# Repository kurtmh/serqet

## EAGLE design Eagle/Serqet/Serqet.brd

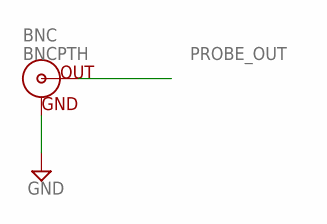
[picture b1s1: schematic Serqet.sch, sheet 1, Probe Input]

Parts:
BNC: BNCPTH; BNC

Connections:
GND: BNC.GND; also elsewhere on the board
PROBE_OUT: BNC.S (OUT); also elsewhere on the board

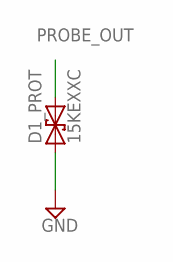
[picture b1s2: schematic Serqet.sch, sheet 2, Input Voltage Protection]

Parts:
D1_PROT: 15KEXXC; CB429-17

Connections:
GND: D1_PROT.A (1); also elsewhere on the board
PROBE_OUT: D1_PROT.C (2); also elsewhere on the board

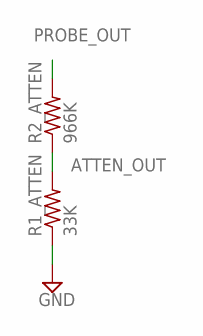
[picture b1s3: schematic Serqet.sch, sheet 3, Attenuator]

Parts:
R1_ATTEN: 33K; R0603
R2_ATTEN: 966K; R0603

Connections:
ATTEN_OUT: R1_ATTEN.2, R2_ATTEN.1; also elsewhere on the board
GND: R1_ATTEN.1; also elsewhere on the board
PROBE_OUT: R2_ATTEN.2; also elsewhere on the board

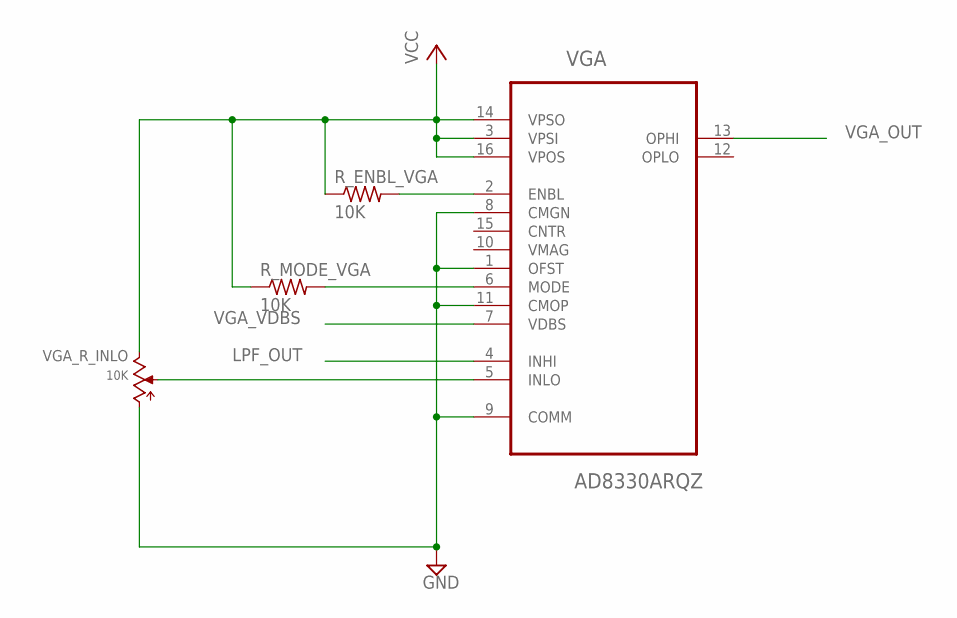
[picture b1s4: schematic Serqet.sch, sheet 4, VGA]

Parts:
R_ENBL_VGA: 10K; R0603
R_MODE_VGA: 10K; R0603
VGA: AD8330ARQZ; SOP63P600X175-16N
VGA_R_INLO: 10K; TRIMPOT:3HOLE_CHEAP

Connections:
GND: VGA.1 (OFST), VGA.8 (CMGN), VGA.9 (COMM), VGA.11 (CMOP), VGA_R_INLO.CCW; also elsewhere on the board
LPF_OUT: VGA.4 (INHI); also elsewhere on the board
unnamed: VGA.5 (INLO), VGA_R_INLO.W
unnamed: R_ENBL_VGA.2, VGA.2 (ENBL)
VCC: R_ENBL_VGA.1, R_MODE_VGA.1, VGA.3 (VPSI), VGA.14 (VPSO), VGA.16 (VPOS), VGA_R_INLO.CW; also elsewhere on the board
VGA_MODE: R_MODE_VGA.2, VGA.6 (MODE)
VGA_OUT: VGA.13 (OPHI); also elsewhere on the board
VGA_VDBS: VGA.7 (VDBS); also elsewhere on the board

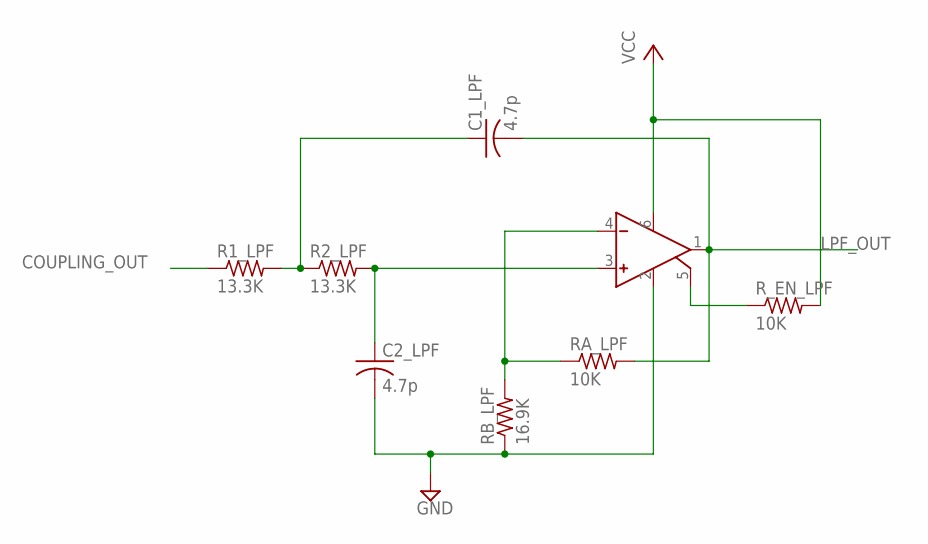
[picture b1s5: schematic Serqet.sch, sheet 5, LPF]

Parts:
C1_LPF, C2_LPF: 4.7p; C0603
OP_AMP_LPF: OPA355; SOT23-6
R1_LPF, R2_LPF: 13.3K; R0603
RA_LPF: 10K; R0603
RB_LPF: 16.9K; R0603
R_EN_LPF: 10K; R0603

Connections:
COUPLING_OUT: R1_LPF.1; also elsewhere on the board
GND: C2_LPF.2, OP_AMP_LPF.2 (GND), RB_LPF.1; also elsewhere on the board
LPF_OUT: C1_LPF.2, OP_AMP_LPF.1 (OUT), RA_LPF.2; also elsewhere on the board
unnamed: C2_LPF.1, OP_AMP_LPF.3 (V+), R2_LPF.2
unnamed: C1_LPF.1, R1_LPF.2, R2_LPF.1
unnamed: OP_AMP_LPF.4 (V-), RA_LPF.1, RB_LPF.2
unnamed: OP_AMP_LPF.5 (ENABLE), R_EN_LPF.1
VCC: OP_AMP_LPF.6 (VCC), R_EN_LPF.2; also elsewhere on the board

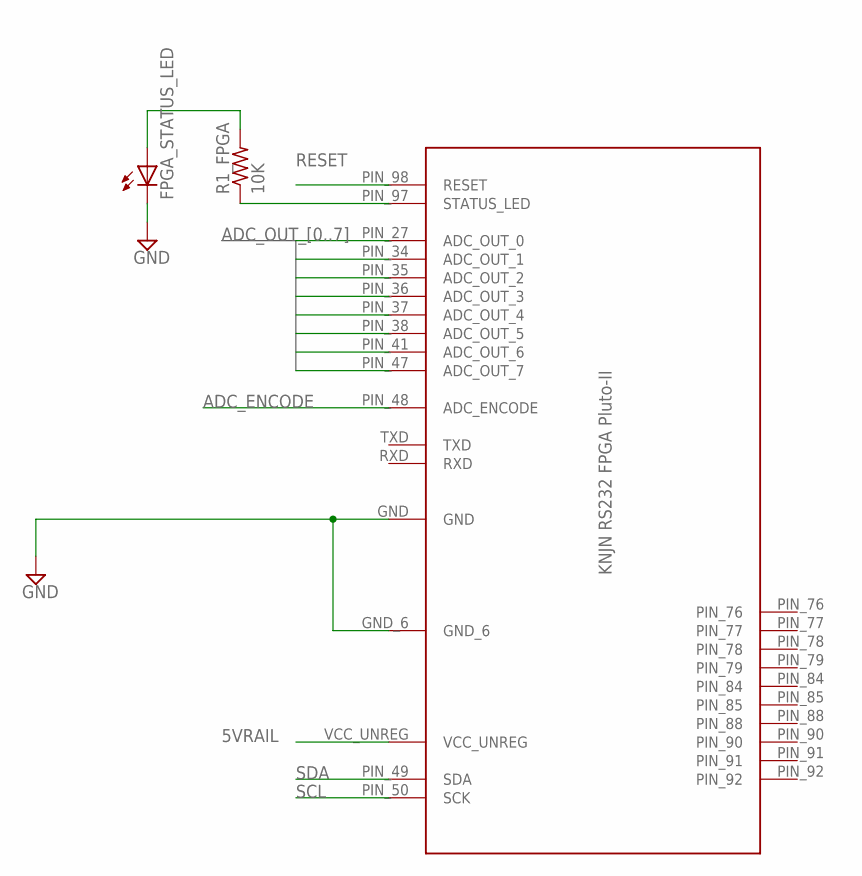
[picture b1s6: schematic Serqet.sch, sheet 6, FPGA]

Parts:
FPGA: KNJNRS232FPGAPLUTO-IIKNJNRS232FPGAPLUTO-II; KNJNRS232FPGAPLUTO-II
FPGA_STATUS_LED: LEDCHIP-LED0805; CHIP-LED0805
R1_FPGA: 10K; R0603

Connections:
5VRAIL: FPGA.VCC_UNREG; also elsewhere on the board
ADC_ENCODE: FPGA.PIN_48 (ADC_ENCODE); also elsewhere on the board
ADC_OUT_0: FPGA.PIN_47 (ADC_OUT_7); also elsewhere on the board
ADC_OUT_1: FPGA.PIN_41 (ADC_OUT_6); also elsewhere on the board
ADC_OUT_2: FPGA.PIN_38 (ADC_OUT_5); also elsewhere on the board
ADC_OUT_3: FPGA.PIN_37 (ADC_OUT_4); also elsewhere on the board
ADC_OUT_4: FPGA.PIN_36 (ADC_OUT_3); also elsewhere on the board
ADC_OUT_5: FPGA.PIN_35 (ADC_OUT_2); also elsewhere on the board
ADC_OUT_6: FPGA.PIN_34 (ADC_OUT_1); also elsewhere on the board
ADC_OUT_7: FPGA.PIN_27 (ADC_OUT_0); also elsewhere on the board
GND: FPGA.GND, FPGA.GND_6, FPGA_STATUS_LED.C; also elsewhere on the board
unnamed: FPGA.PIN_97 (STATUS_LED), R1_FPGA.1
unnamed: FPGA_STATUS_LED.A, R1_FPGA.2
RESET: FPGA.PIN_98 (RESET); also elsewhere on the board
SCL: FPGA.PIN_50 (SCK); also elsewhere on the board
SDA: FPGA.PIN_49 (SDA); also elsewhere on the board

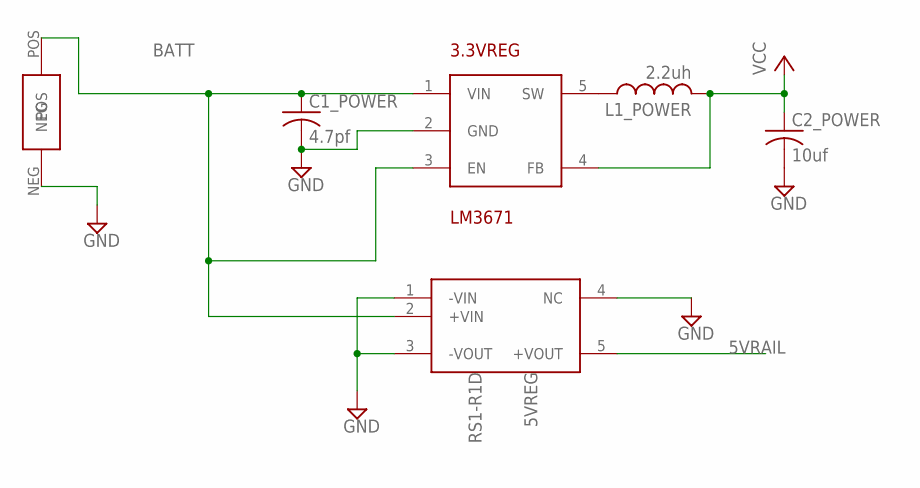
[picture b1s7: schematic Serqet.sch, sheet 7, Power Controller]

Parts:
3.3VREG: LM3671; SOT23-5
5VREG: RS1-R1D; 8-SMD
BATTERY: LED_THROUGHHOLE
C1_POWER: 4.7pf; C0603
C2_POWER: 10uf; C0603
L1_POWER: 2.2uh; L1812

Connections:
5VRAIL: 5VREG.5 (+VOUT); also elsewhere on the board
BATT: 3.3VREG.1 (VIN), 3.3VREG.3 (EN), 5VREG.2 (+VIN), BATTERY.POS, C1_POWER.1
GND: 3.3VREG.2 (GND), 5VREG.1 (-VIN), 5VREG.3 (-VOUT), 5VREG.4 (NC), BATTERY.NEG, C1_POWER.2, C2_POWER.2; also elsewhere on the board
unnamed: 3.3VREG.5 (SW), L1_POWER.1
VCC: 3.3VREG.4 (FB), C2_POWER.1, L1_POWER.2; also elsewhere on the board

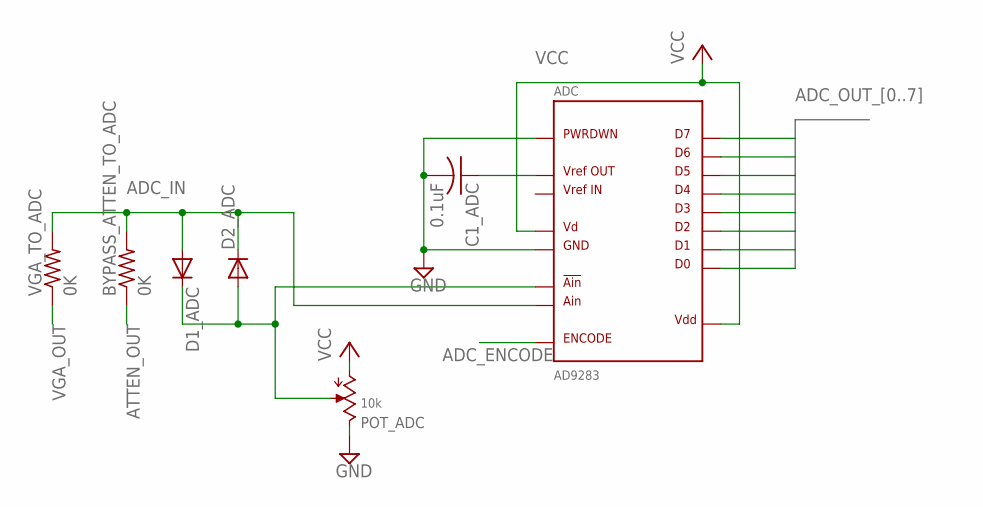
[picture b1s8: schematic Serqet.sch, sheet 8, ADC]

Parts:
ADC: AD9283; SSOP20
BYPASS_ATTEN_TO_ADC: 0K; R0603
C1_ADC: 0.1uF; C0603
D1_ADC, D2_ADC: 1N4933; DO41-10
POT_ADC: 10k; TRIMPOT:3HOLE_CHEAP
VGA_TO_ADC: 0K; R0603

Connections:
ADC_ENCODE: ADC.10 (ENCODE); also elsewhere on the board
ADC_IN: ADC.7 (AIN), BYPASS_ATTEN_TO_ADC.2, D1_ADC.A, D2_ADC.C, VGA_TO_ADC.2
ADC_OUT_0: ADC.20 (D0); also elsewhere on the board
ADC_OUT_1: ADC.19 (D1); also elsewhere on the board
ADC_OUT_2: ADC.18 (D2); also elsewhere on the board
ADC_OUT_3: ADC.17 (D3); also elsewhere on the board
ADC_OUT_4: ADC.14 (D4); also elsewhere on the board
ADC_OUT_5: ADC.13 (D5); also elsewhere on the board
ADC_OUT_6: ADC.12 (D6); also elsewhere on the board
ADC_OUT_7: ADC.11 (D7); also elsewhere on the board
ATTEN_OUT: BYPASS_ATTEN_TO_ADC.1; also elsewhere on the board
GND: ADC.1 (PWRDWN), ADC.4 (GND), ADC.9 (GND), ADC.16 (GND), C1_ADC.2, POT_ADC.CW; also elsewhere on the board
unnamed: ADC.2 (VREFOUT), C1_ADC.1
unnamed: ADC.6 (!AIN), D1_ADC.C, D2_ADC.A, POT_ADC.W
VCC: ADC.5 (VD), ADC.8 (VD), ADC.15 (VDD), POT_ADC.CCW; also elsewhere on the board
VGA_OUT: VGA_TO_ADC.1; also elsewhere on the board
VREFIN: ADC.3 (VREFIN)

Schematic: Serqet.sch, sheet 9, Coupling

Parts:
BILATERAL_COUPLING: TC74HC4066AFT; TSSOP14
C1_COUPLING: 9.1nF; C0603
OP_AMP_COUPLING: OPA355; SOT23-6
POT_COUPLING: 10K; TRIMPOT:3HOLE_CHEAP
R1_COUPLING, R2_COUPLING, R3_COUPLING, R4_COUPLING, R5_COUPLING: 10K; R0603

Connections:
AC_COUPLING_IN: BILATERAL_COUPLING.2 (O/I_1), C1_COUPLING.1, R1_COUPLING.1
AC_EN: BILATERAL_COUPLING.6 (C_3), BILATERAL_COUPLING.13 (C_1), OP_AMP_COUPLING.5 (ENABLE); also elsewhere on the board
ADJ_DC_OFFSET: BILATERAL_COUPLING.11 (I/O_4); also elsewhere on the board
COUPLING_OPAMP_OUT: BILATERAL_COUPLING.8 (I/O_3), OP_AMP_COUPLING.1 (OUT), R5_COUPLING.2
COUPLING_OUT: BILATERAL_COUPLING.3 (O/I_2), BILATERAL_COUPLING.9 (O/I_3); also elsewhere on the board
DC_EN: BILATERAL_COUPLING.5 (C_2); also elsewhere on the board
DC_OFFSET_OUT: BILATERAL_COUPLING.1 (I/O_1), BILATERAL_COUPLING.4 (I/O_2); also elsewhere on the board
GND: BILATERAL_COUPLING.7 (GND), OP_AMP_COUPLING.2 (GND), POT_COUPLING.CCW, R1_COUPLING.2, R4_COUPLING.2; also elsewhere on the board
unnamed: OP_AMP_COUPLING.3 (V+), R2_COUPLING.2, R3_COUPLING.2
unnamed: OP_AMP_COUPLING.4 (V-), R4_COUPLING.1, R5_COUPLING.1
unnamed: C1_COUPLING.2, R2_COUPLING.1
OFST: POT_COUPLING.W, R3_COUPLING.1
POS_OFFSET: BILATERAL_COUPLING.10 (O/I_4); also elsewhere on the board
POS_OFFSET_EN: BILATERAL_COUPLING.12 (C_4); also elsewhere on the board
VCC: BILATERAL_COUPLING.14 (VCC), OP_AMP_COUPLING.6 (VCC), POT_COUPLING.CW; also elsewhere on the board

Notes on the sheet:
bilateral switch used in DC Offset

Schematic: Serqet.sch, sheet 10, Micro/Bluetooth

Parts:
BYPASS_ATTEN_MICRO: 0K; R0603
LED_THROUGHOLE: LED_THROUGHHOLE
MICRO: MICROCONTROLLER; MICROPROC
MICRO_STATUS_LED: LEDCHIP-LED0805; CHIP-LED0805
PAIRING_SWITCH: LED_THROUGHHOLE
R1_MICRO, R2_MICRO, R3_MICRO, R4_MICRO, R5_MICRO: 10K; R0603

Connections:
AC_EN: MICRO.3 (AC_EN); also elsewhere on the board
ATTEN_OUT: BYPASS_ATTEN_MICRO.1; also elsewhere on the board
DC_EN: MICRO.4 (DC_EN); also elsewhere on the board
GND: LED_THROUGHOLE.NEG, MICRO.5 (GND), MICRO.12 (GND2), MICRO_STATUS_LED.C, R5_MICRO.1; also elsewhere on the board
unnamed: MICRO.14 (STATUS_LED), R3_MICRO.2
unnamed: MICRO_STATUS_LED.A, R3_MICRO.1
unnamed 43: MICRO.9 (PAIRING_BUTTON), PAIRING_SWITCH.NEG, R5_MICRO.2; also elsewhere on the board
unnamed: MICRO.7 (PAIRING_LED), R4_MICRO.2
unnamed: LED_THROUGHOLE.POS, R4_MICRO.1
unnamed: BYPASS_ATTEN_MICRO.2, MICRO.8 (BYPASS_ADC)
NEG_OFFSET_EN: MICRO.11 (NEG_EN); also elsewhere on the board
POS_OFFSET_EN: MICRO.10 (POS_EN); also elsewhere on the board
RESET: MICRO.15 (RESET); also elsewhere on the board
SCL: MICRO.13 (SCL), R2_MICRO.1; also elsewhere on the board
SDA: MICRO.16 (SDA), R1_MICRO.1; also elsewhere on the board
VCC: MICRO.6 (V_IN), PAIRING_SWITCH.POS, R1_MICRO.2, R2_MICRO.2; also elsewhere on the board

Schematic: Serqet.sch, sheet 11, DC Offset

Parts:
BILATERAL_DCOFF: TC74HC4066AFT; TSSOP14
OP_AMP1_DCOFF, OP_AMP2_DCOFF: OPA355; SOT23-6
R1_DCOFF, R2_DCOFF, R3_DCOFF, R4_DCOFF, R5_DCOFF, R6_DCOFF, R7_DCOFF, R8_DCOFF: 10K; R0603
R_OFFSET_BYPASS: 0K; R0603

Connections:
ADJ_DC_OFFSET: R5_DCOFF.1; also elsewhere on the board
ATTEN_OUT: R_OFFSET_BYPASS.1; also elsewhere on the board
DC_OFFSET_OUT: BILATERAL_DCOFF.9 (O/I_3), BILATERAL_DCOFF.10 (O/I_4); also elsewhere on the board
GND: BILATERAL_DCOFF.7 (GND), OP_AMP1_DCOFF.2 (GND), OP_AMP2_DCOFF.2 (GND), R4_DCOFF.2, R8_DCOFF.2; also elsewhere on the board
unnamed: OP_AMP1_DCOFF.4 (V-), R3_DCOFF.1, R4_DCOFF.1
unnamed: OP_AMP1_DCOFF.3 (V+), R1_DCOFF.2, R2_DCOFF.2
unnamed: BILATERAL_DCOFF.11 (I/O_4), OP_AMP1_DCOFF.1 (OUT), R3_DCOFF.2
unnamed: OP_AMP2_DCOFF.3 (V+), R6_DCOFF.2, R8_DCOFF.1
unnamed: OP_AMP2_DCOFF.4 (V-), R5_DCOFF.2, R7_DCOFF.1
unnamed: BILATERAL_DCOFF.8 (I/O_3), OP_AMP2_DCOFF.1 (OUT), R7_DCOFF.2
unnamed: BILATERAL_DCOFF.2 (O/I_1), R6_DCOFF.1
unnamed 43: BILATERAL_DCOFF.3 (O/I_2), R2_DCOFF.1; also elsewhere on the board
NEG_OFFSET_EN: BILATERAL_DCOFF.6 (C_3), BILATERAL_DCOFF.13 (C_1), OP_AMP2_DCOFF.5 (ENABLE); also elsewhere on the board
NET_IO_1: BILATERAL_DCOFF.1 (I/O_1), BILATERAL_DCOFF.4 (I/O_2), R_OFFSET_BYPASS.2
POS_OFFSET: R1_DCOFF.1; also elsewhere on the board
POS_OFFSET_EN: BILATERAL_DCOFF.5 (C_2), BILATERAL_DCOFF.12 (C_4), OP_AMP1_DCOFF.5 (ENABLE); also elsewhere on the board
VCC: BILATERAL_DCOFF.14 (VCC), OP_AMP1_DCOFF.6 (VCC), OP_AMP2_DCOFF.6 (VCC); also elsewhere on the board

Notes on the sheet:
Voltage Summer
Voltage Subtractor
See coupling for bilateral switch

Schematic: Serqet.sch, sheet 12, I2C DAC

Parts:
C4: 0.1uF; C0603
DAC: LTC2633CTS8-LZ8TRMPBF; SOT65P280X100-8N

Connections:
ADJ_DC_OFFSET: DAC.5 (VOUTA); also elsewhere on the board
GND: C4.2, DAC.2 (CA0), DAC.4 (GND); also elsewhere on the board
unnamed: C4.1, DAC.3 (REF)
SCL: DAC.1 (SCL); also elsewhere on the board
SDA: DAC.8 (SDA); also elsewhere on the board
VCC: DAC.7 (VCC); also elsewhere on the board
VGA_VDBS: DAC.6 (VOUTB); also elsewhere on the board

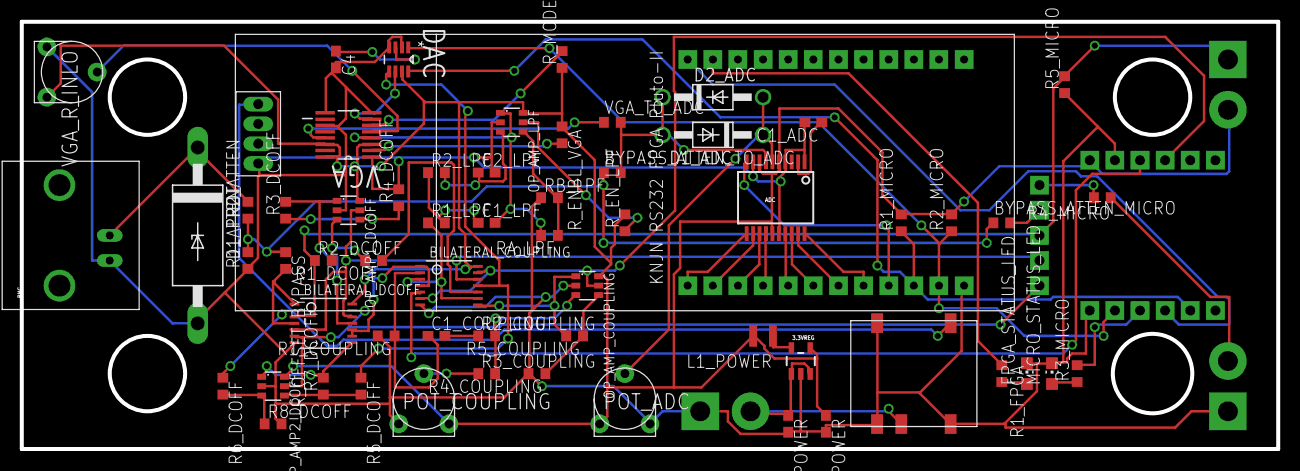
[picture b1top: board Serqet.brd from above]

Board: 2 copper layers, 127.0 x 43.2 mm, 65 parts (0 on the bottom side), 63 nets.

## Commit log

2014-07-24 First commit of temporary Arduino code
2014-07-24 removed Arduino folder from master
2014-07-24 First commit of temporary Arduino sketch
2015-03-09 Initial Eagle import from GDrive
2015-03-09 fixed probe net name
2015-03-09 Removed Library Cruft
2015-03-09 Added DC offset
2015-03-09 Added project and library cruft to git ignore
2015-03-09 Removed Quad Bilateral Switch sheets
2015-03-09 Added most of Adj DC Offset
2015-03-09 Fixed net name
2015-03-09 Microprocessor added
2015-03-09 Power Controller Boost update
2015-03-09 Conneced last bilateral switch
2015-03-09 Cleaned up coupling and ADC
2015-03-09 Settings update
2015-03-09 Moved text to info layer
2015-03-09 Changed 3V3Rail net to Vcc
2015-03-09 Added bus to ADC out
2015-03-10 Temp branch to fix FPGA layout
2015-03-10 Cleaned up FPGA symbol
2015-03-10 Finished FPGA layout changes
2015-03-10 Added FPGA to sheet
2015-03-10 Added power controller component values
2015-03-10 Completed FPGA sheet
2015-03-10 Updated space between FPGA board and TXDI connector on our PCB
2015-03-10 Updated FPGA library and schematic to add 4 new pin functions
2015-03-10 Updated Microprocessor footprint
2015-03-10 Moved new FPGA Pins
2015-03-10 Added I2C DAC
2015-03-10 Began Status and Bluetooth LEDs on MCU
2015-03-10 Added I2C nets
2015-03-10 Added LED_THROUGHHOLE footprint
2015-03-10 Added FPGA status LED
2015-03-10 Swapped VGA INLO voltage divider for a trimpot
2015-03-10 Renamed VGA trimpot
2015-03-11 Added additional nets to micro and DAC
2015-03-11 Added micro status led
2015-03-11 Added custom 3-pin switch package and Bluetooth switch
2015-03-11 Renamed SUPPLY25 to BLUETOOTH_GND in MCU sheet
2015-03-11 Removed drill holes from FPGA
2015-03-11 Removed drill holes from micro
2015-03-11 Updated micro and FPGA libraries
2015-03-11 Changed to the real BNC
2015-03-11 Fix GND connection on BNC
2015-03-11 removed unnessesary fpga connections
2015-03-11 Added MCU Pairing LED and 2 pin throughhole library
2015-03-12 Updated FPGA in the schematic
2015-03-12 Completed DAC
2015-03-12 Replaced battery connection and renamed parts
2015-03-12 Renamed some parts
2015-03-12 Renamed adc, coupling and dc offset
2015-03-12 updated micro pins
2015-03-12 add nets for reset and bypass adc
2015-03-12 Added bypass resistors
2015-03-12 Updated names
2015-03-12 Updated more names
2015-03-12 Updated MOAR names
2015-03-12 Updated FPGA hole diameters
2015-03-12 Reversed direction of FPGA_STATUS_LED
2015-03-12 Removed LPF Enable
2015-03-12 Updated LED throughhole diameter
2015-03-12 Fixed LPF and VGA enables
2015-03-12 Fixed signal conditioning bypass
2015-03-12 Changed coupling capacitor value to one that exists on DigiKey
2015-03-12 Initial board
2015-03-12 Added board dim. Added board cruft to git ignore
2015-03-12 Added mount holes
2015-03-12 Inverted bit order between ADC and FPGA for better layout
2015-03-12 Started Placing parts
2015-03-12 Inital part placement
2015-03-12 Added autorouting control file
2015-03-12 Spaced parts out
2015-03-12 More spacing, updated design rules
2015-03-12 Updated pads to prevent routing between them. Autorouted!
2015-03-13 Added BOM
2015-03-13 Reordered sheets to reflect signal path

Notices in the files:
parts and their libraries:
SparkFun-DigitalIC: Licensing: Creative Commons ShareAlike 4.0 International - https://creativecommons.org/licenses/by-sa/4.0
